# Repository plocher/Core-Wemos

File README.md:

# Core-Wemos
## License: CERN Open Hardware Licence v1.2

Based on cost and features, the WeMOS ESP8366 board is the next logical step up from the ProMini for my control point work.

Previous boards (Core-ArdIOShield, Core-ESP8266, Core-OAK, Core-PhotonIOShield and Core-Multi - not published here) were useful learning experiences,
but their limitations (ArdIOShield has no wifi, OAK is a failed KickStarter, Photon is expensive and aimed at a different user base, ...)
mean I won't be using them any more...

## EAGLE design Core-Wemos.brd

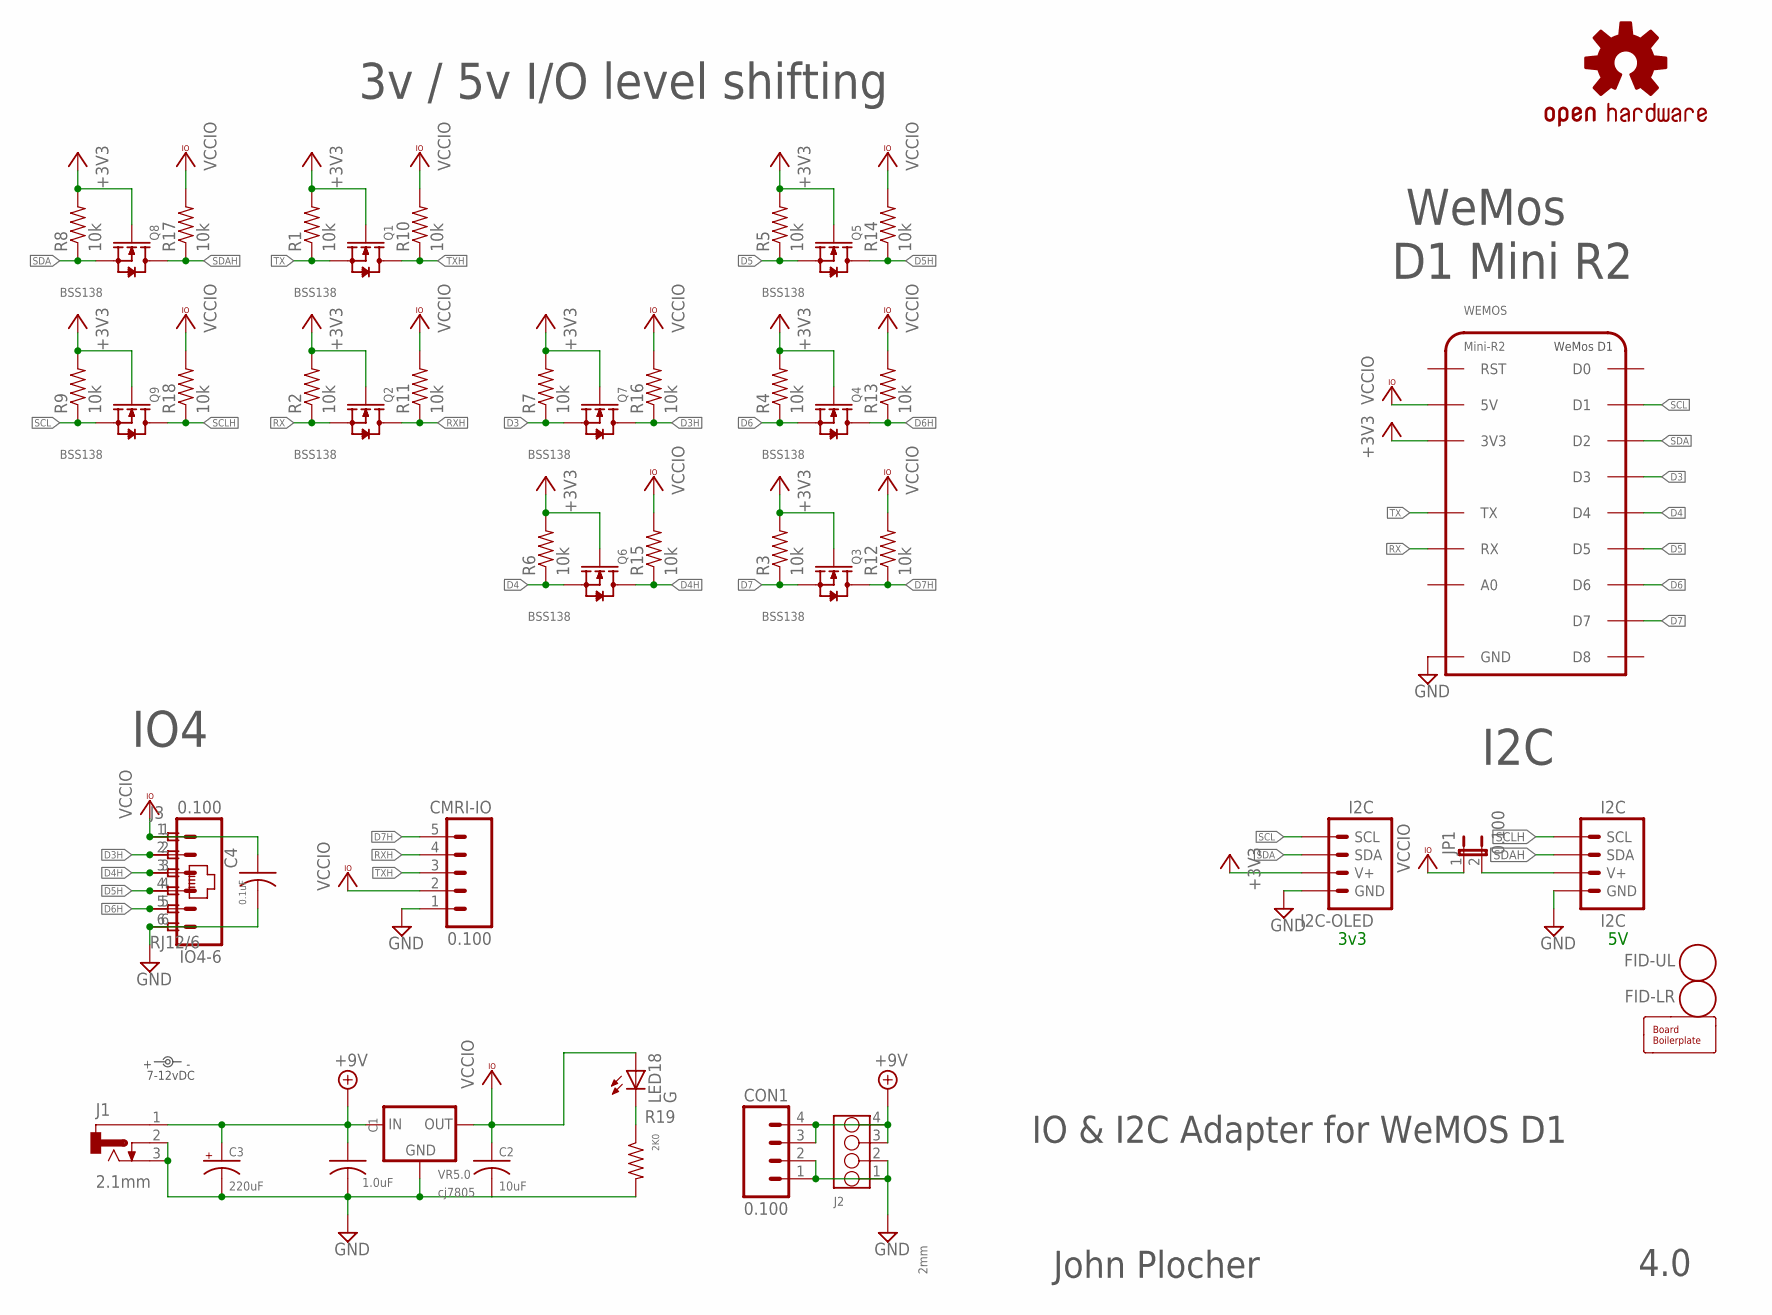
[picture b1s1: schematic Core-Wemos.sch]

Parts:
BOARD: BOARD; BOARD-DINRAIL-3.17INX8CM-NOHOLES
C1: 1.0uF; 0603-CAP
C2: 10uF; 0603-CAP
C3: 220uF; 0810-CAP
C4: 0.1uF; 0603-CAP
CMRI-IO: 0.100; 1X05-CMRI-IO
CON1: 0.100; 1X04_LOCK
FID-LR: FIDUCIAL; FIDUCIAL_1MM
FID-UL: FIDUCIAL; FIDUCIAL_1MM
I2C: I2C; I2C-L
I2C-OLED: I2C; I2C-NOOUTLINE
IO4-6: 0.100; 1X06_LOCK
J1: 2.1mm; DCJ0202
J2: 2mm; 4P-2.0
J3: RJ12/6; RJ25-PANEL
JP1: 0.100; 1X02_LOCK
LABEL1: 7-12vDC; PWR_LABEL
LED18: G; 0603-LED
OSHW1: OSHW; OSHW-LOGO-L
Q1, Q2, Q3, Q4, Q5, Q6, Q7, Q8, Q9: BSS138; SOT23
R1, R2, R3, R4, R5, R6, R7, R8, R9, R10, R11, R12, R13, R14, R15, R16, R17, R18: 10k; 0603-RES
R19: 2K0; 0603-RES
VR5.0: cj7805; TO-252
WEMOS: Mini-R2; WEMOS-D1

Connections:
+3V3: I2C-OLED.V+, Q1.1 (G), Q2.1 (G), Q3.1 (G), Q4.1 (G), Q5.1 (G), Q6.1 (G), Q7.1 (G), Q8.1 (G), Q9.1 (G), R1.2, R2.2, R3.2, R4.2, R5.2, R6.2, R7.2, R8.2, R9.2, WEMOS.3V3
+9V: C1.1, C3.+, CON1.3, CON1.4, J1.1, J2.3, J2.4, VR5.0.1 (IN)
D3: Q7.2 (S), R7.1, WEMOS.D3
D3H: IO4-6.2, J3.2, Q7.3 (D), R16.1
D4: Q6.2 (S), R6.1, WEMOS.D4
D4H: IO4-6.3, J3.3, Q6.3 (D), R15.1
D5: Q5.2 (S), R5.1, WEMOS.D5
D5H: IO4-6.4, J3.4, Q5.3 (D), R14.1
D6: Q4.2 (S), R4.1, WEMOS.D6
D6H: IO4-6.5, J3.5, Q4.3 (D), R13.1
D7: Q3.2 (S), R3.1, WEMOS.D7
D7H: CMRI-IO.5, Q3.3 (D), R12.1
GND: C1.2, C2.2, C3.-, C4.2, CMRI-IO.1, CON1.1, CON1.2, I2C.GND, I2C.GND@1 (GND), I2C-OLED.GND, IO4-6.6, J1.2, J1.3, J2.1, J2.2, J3.6, VR5.0.2 (GND), WEMOS.GND
GND1: R19.2
unnamed: LED18.C, R19.1
unnamed: I2C.V+, I2C.V+@1 (V+), JP1.2
RX: Q2.2 (S), R2.1, WEMOS.RX
RXH: CMRI-IO.4, Q2.3 (D), R11.1
SCL: I2C-OLED.SCL, Q9.2 (S), R9.1, WEMOS.D1
SCLH: I2C.SCL, I2C.SCL@1 (SCL), Q9.3 (D), R18.1
SDA: I2C-OLED.SDA, Q8.2 (S), R8.1, WEMOS.D2
SDAH: I2C.SDA, I2C.SDA@1 (SDA), Q8.3 (D), R17.1
TX: Q1.2 (S), R1.1, WEMOS.TX
TXH: CMRI-IO.3, Q1.3 (D), R10.1
VCCIO: C2.1, C4.1, CMRI-IO.2, IO4-6.1, J3.1, JP1.1, LED18.A, R10.2, R11.2, R12.2, R13.2, R14.2, R15.2, R16.2, R17.2, R18.2, VR5.0.3 (OUT), WEMOS.5V

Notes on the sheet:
IO & I2C Adapter for WeMOS D1
John Plocher
4.0
I2C
WeMos D1 Mini R2
3v / 5v I/O level shifting
IO4
3v3

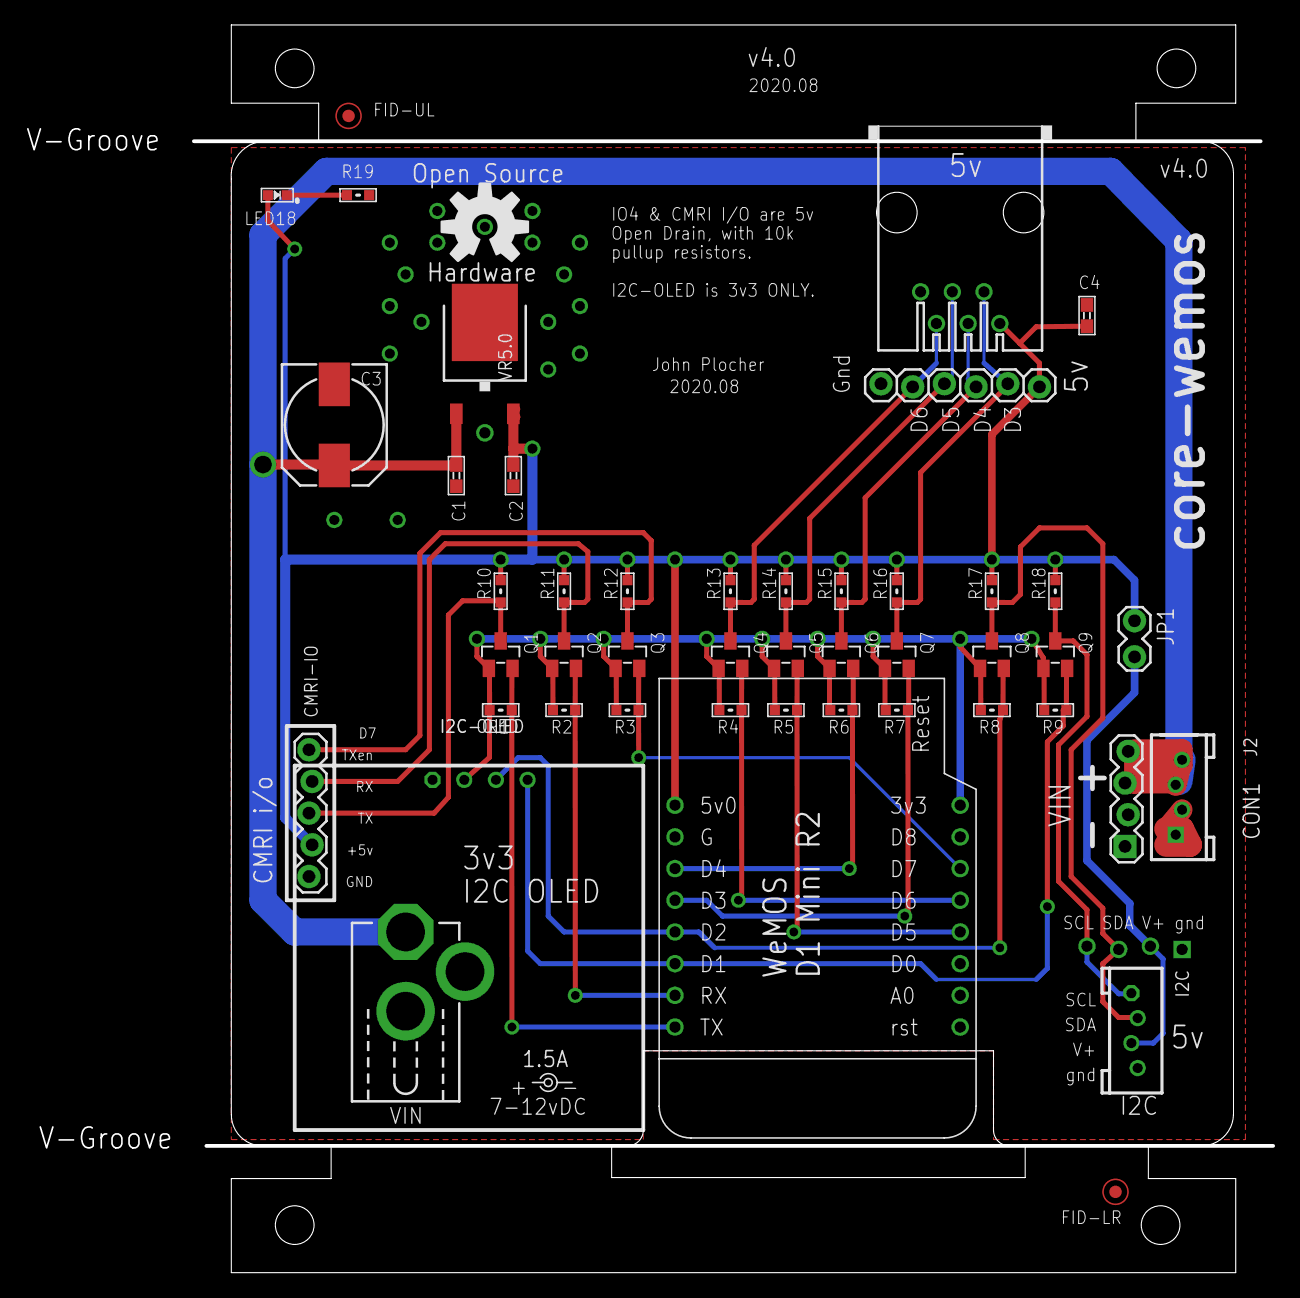
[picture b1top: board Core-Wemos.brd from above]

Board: 2 copper layers, 99.9 x 99.7 mm, 49 parts (0 on the bottom side), 24 nets.

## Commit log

2019-12-07 added graphic
2020-05-04 updated tags
2020-07-29 removed Matrix display, added OLED, shrunk
2020-07-29 fixed back silk
2020-07-29 realigned I2C connectors, added power on LED
2020-07-29 Silkscreen 4.0 change
2020-07-30 normaliized drills
2020-08-06 Moved OLED, added 1x4 0.100 VIN
2020-08-12 Renamed/Moved FIDs
2020-09-19 added missing component values
2020-09-19 updated part names and values
2020-09-19 FIDs
2020-09-19 updated part names
2020-10-06 normalized values
